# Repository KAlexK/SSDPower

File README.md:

# SSDPower
 Measurement of power consumption of PCIe SSD with M.2 connector.
 
 Schematic diagram:

 Ready device:

 Assembled device on the adapter:

 Front side of the adapter:

 The description will be published [at this link (in Russian)](https://www.ixbt.com/data/ssd-power-test.html).

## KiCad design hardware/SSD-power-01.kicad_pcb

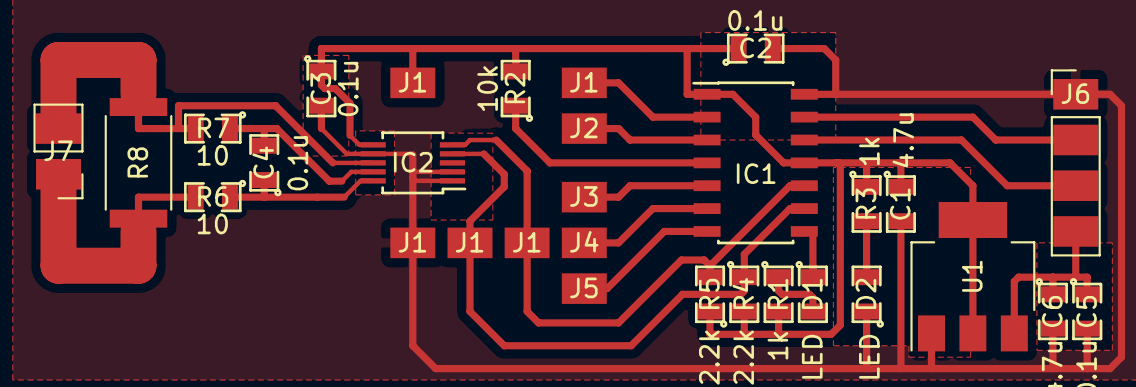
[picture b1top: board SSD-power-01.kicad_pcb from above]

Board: 2 copper layers, 30 parts (0 on the bottom side), 20 nets.

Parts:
C1, C6: 4.7u; SMD-0805
C2, C3, C4, C5: 0.1u; SMD-0805
D1, D2: LED; SMD-0805
IC1: MCP2221; SOIC-14_3.9x8.7mm_Pitch1.27mm
IC2: INA226; MSOP-10_3x3mm_Pitch0.5mm
J1, J1#2, J1#3, J1#4, J1#5, J2, J3, J4, J5: Conn_01x01; Measurement_Point_Square-SMD-Pad_Big
J6: Conn_01x04; Pin_Header_Straight_1x04_Pitch2.54mm
J7: Conn_01x02; Pin_Header_Straight_1x02_Pitch2.54mm
R1, R3: 1k; SMD-0805
R2: 10k; SMD-0805
R4, R5: 2.2k; SMD-0805
R6, R7: 10; SMD-0805
R8: 0.025; R_2512
U1: LM1117-3.3; SOT-223-3_TabPin2

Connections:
GND: C1.2, C2.2, C3.2, C5.2, C6.2, D2.1, IC1.14, IC2.1, IC2.2, IC2.7, J1#3.1, J6.1, U1.1
unnamed: C4.1, IC2.10, R6.1
unnamed: C4.2, IC2.9, R7.1
unnamed: C5.1, C6.1, J6.4, U1.3
unnamed: D1.1, IC1.8
unnamed: D1.2, R1.1
unnamed: D2.2, R3.2
unnamed: IC1.2, J1#5.1
unnamed: IC1.3, J2.1
unnamed: IC1.4, R2.1
unnamed: IC1.5, J3.1
unnamed: IC1.6, J4.1
unnamed: IC1.7, J5.1
unnamed: IC1.9, IC2.4, J1.1, R4.1
unnamed: IC1.10, IC2.5, J1#2.1, R5.2
unnamed: IC1.12, J6.3
unnamed: IC1.13, J6.2
unnamed: IC2.8, J7.2, R7.2, R8.1
unnamed: J7.1, R6.2, R8.2
VDD: C1.1, C2.1, C3.1, IC1.1, IC1.11, IC2.6, J1#4.1, R1.2, R2.2, R3.1, R4.2, R5.1, U1.2

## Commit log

2022-02-28 Files added
2022-03-01 Release 1.0
